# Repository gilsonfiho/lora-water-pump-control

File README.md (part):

# Controle de Bomba D'água à Distância — ESP32-C3 + LoRa

Sistema de controle remoto de bomba d'água com dois nós sem fio de longo
alcance (até ~5 km), baseado em **ESP32-C3** e módulos **LoRa EBYTE E220**
(900 MHz). O nó do reservatório mede o nível da caixa d'água e comanda, via
LoRa, o nó da bomba na captação — com confirmação (ACK), retransmissão e
**failsafe de segurança** (a bomba desliga se o enlace cair).

> **Status do projeto:** 🟡 `v0.0.1` (estruturação, pré-alpha) — esqueleto
> funcional. Arquitetura, protocolo e drivers principais implementados. Pinagem
> e modelo exato dos módulos ainda precisam ser confirmados no hardware —
> procure por `TODO(hw)` no código. Histórico em [`CHANGELOG.md`](CHANGELOG.md).
>
> A branch `feature/prototipo-bancada` roda em **modo bancada**: ver
> [Protótipo de bancada](#protótipo-de-bancada).

---

## Sumário

- [Visão geral](#visão-geral)
- [Hardware necessário](#hardware-necessário)
- [Estrutura do repositório](#estrutura-do-repositório)
- [Como compilar e gravar](#como-compilar-e-gravar)
- [Testes automatizados](#testes-automatizados)
- [Protótipo de bancada](#protótipo-de-bancada)
- [Configuração](#configuração)
- [Protocolo de comunicação](#protocolo-de-comunicação)
- [Documentação adicional](#documentação-adicional)
- [Pendências (TODOs de hardware)](#pendências-todos-de-hardware)

---

## Visão geral

| Nó | Papel | Componentes | Seleção |
|----|-------|-------------|---------|
| **Reservatório** | Transmissor | ESP32-C3, boia de nível, E220 | strap aberto |
| **Bomba** | Receptor / atuador | ESP32-C3, relé/contator, E220 | strap no GND |

**Lógica de controle (com histerese das boias):**

- Caixa **baixa** → comando **LIGAR** bomba (encher).
- Caixa **cheia** → comando **DESLIGAR** bomba.
- Nível intermediário → mantém o comando anterior (evita liga-desliga rápido).
- Falha de sensor **ou perda de enlace** → bomba **DESLIGADA** (seguro).

## Hardware necessário

- 2× **ESP32-C3** (RISC-V, Wi-Fi + BLE, baixo consumo).
- 2× módulo LoRa **EBYTE E220-900T30D** (30 dBm / 1 W) **ou** **E220-900T22D**
  (22 dBm / 160 mW) — o firmware suporta ambos (só muda a tabela de potência).
  O protótipo usa o **par T30D**, e o T22D entra como comparação no teste de
  campo.
  > ⚠️ Os E220 são **UART/TTL**, não SPI. A camada HAL abstrai isso; um driver
  > SPI SX1276/RFM95 existe como **segunda estratégia** (esqueleto).
- Sensor de nível: **boia** (padrão) — 1 ou 2 boias para histerese.
  Ultrassônico é **opcional** (flag `USE_ULTRASONIC_SENSOR`).
- 1× **relé/contator** dimensionado para a bomba (no nó da bomba).
- Alimentação **dual com failover** por nó:
  - Fonte externa (adaptador 5 V / 12 V) **+**
  - Bateria de lítio 18650 com carregador/proteção (**TP4056** ou similar);
  - Chaveamento automático fonte↔bateria (ideal-diode/diodos);
  - Monitor de tensão/corrente (ADC via divisor, ou **INA219/INA226** por I2C).
- Antenas SMA adequadas à faixa 900 MHz (ganho ~2–3 dBi).

### Ligações dos nós

| Reservatório (transmissor) | Bomba (receptor/atuador) |
|:--------------------------:|:------------------------:|
|  |  |

> Esquemático completo, pinagem detalhada e notas de projeto:
> [`assets/schematic.md`](assets/schematic.md).

### Placas (PCB)

Duas placas em KiCad 10 (`hardware/`), ESP32-C3-MINI-1 + soquete para o E220,
2 camadas. Versão atual: `hw-v0.2` (inclui o LED de RSSI).

| Emissor (reservatório) | Receptor (bomba) |
|:----------------------:|:----------------:|
|  |  |
|  |  |
|  |  |
| [STEP](hardware/fab/emissor/emissor.step) | [STEP](hardware/fab/receptor/receptor.step) |

> Decisões de projeto, regras de layout e como abrir os projetos:
> [`hardware/README.md`](hardware/README.md) e
> [`hardware/docs/decisoes.md`](hardware/docs/decisoes.md).

## Estrutura do repositório

```
lora-water-pump-control/
├── CMakeLists.txt              # projeto ESP-IDF
├── sdkconfig.defaults          # alvo esp32c3 + opções do projeto
├── README.md
├── CHANGELOG.md                # histórico de versões (SemVer)
├── docs/
│   ├── ARCHITECTURE.md         # decisões, camadas, protocolo, máquinas de estado
│   ├── context/                # notas de contexto (decisões, hardware, status)
│   └── datasheets/             # manuais dos módulos E220
├── assets/
│   ├── block-diagram.md/.svg   # diagrama de blocos da solução
│   ├── schematic.md            # esquemático elétrico (imagens + Mermaid + texto)
│   ├── schematic-power.svg     # subsistema de energia (failover + TP4056)
│   ├── schematic-reservoir.svg # ligações do nó do reservatório
│   └── schematic-pump.svg      # ligações do nó da bomba
├── components/                 # código compartilhado, em camadas
│   ├── config/                 # pinos, endereços, timeouts, perfil de RF
│   ├── platform/               # relógio monotônico (isola o ESP-IDF)
│   ├── hw/                     # abstração de hardware (interfaces + drivers)
│   ├── protocol/               # pacote, CRC, camada de enlace (ACK/retry)
│   ├── core/                   # máquinas de estado + Observer
│   └── power/                  # deep sleep + failover de energia
└── main/
    ├── main.cpp                # lê o strap e assume o papel do nó
    ├── reservoir_app.cpp       # laço do nó do reservatório
    └── pump_app.cpp            # laço do nó da bomba
```

As dependências entre camadas são declaradas em `REQUIRES`, no `CMakeLists.txt`
de cada componente — o build **impede** que `core/` ou `protocol/` alcancem um
driver concreto.

## Como compilar e gravar

O projeto é compilado e gravado pela **extensão ESP-IDF do VS Code**, com o
[ESP-IDF](https://docs.espressif.com/projects/esp-idf/) **v6.1**.

**Um único binário serve aos dois nós.** O papel é lido no boot pelo pino
`cfg::RolePins::kRoleStrap`:

| Strap | Papel |
|-------|-------|
| aberto | reservatório (transmissor) |
| ligado ao GND | bomba (receptor/atuador) |

O aberto virar reservatório é proposital: é o papel que não aciona o relé, então
um strap solto nunca faz um nó assumir o comando da bomba.

### Preparação (uma vez por máquina)

1. Instale a extensão **ESP-IDF** (`espressif.esp-idf-extension`) no VS Code.
2. `Ctrl+Shift+P` → **ESP-IDF: Configure ESP-IDF Extension**. O instalador
   (EIM) baixa o ESP-IDF **v6.1** e as ferramentas (no Windows, em `C:\esp\v6.1`
   e `C:\Espressif`).
3. Abra a pasta do repositório no VS Code.
4. `Ctrl+Shift+P` → **ESP-IDF: Select Current ESP-IDF Version** → **v6.1**.

### Configuração do projeto (uma vez)

Pela barra de status, na parte de baixo da janela, ou pela paleta
(`Ctrl+Shift+P`):

| Ajuste | Comando | Valor |
|--------|---------|-------|
| Alvo | **ESP-IDF: Set Espressif Device Target** | `esp32c3` → *ESP32-C3 chip (via builtin USB-JTAG)* |
| Método de gravação | **ESP-IDF: Select Flash Method** | `UART` |
| Porta | **ESP-IDF: Select Port to Use** | a COM da placa (ex.: `COM3`) |

Trocar o alvo recria o `sdkconfig` a partir do `sdkconfig.defaults`. A porta
aparece no Gerenciador de Dispositivos (o USB Serial/JTAG do C3 costuma se
chamar "Dispositivo serial USB").

### Comandos da extensão

| Ação | Atalho | Comando da paleta |
|------|--------|-------------------|
| Compilar | `Ctrl+E B` | ESP-IDF: Build your Project |
| Gravar | `Ctrl+E F` | ESP-IDF: Flash your Project |
| Monitor serial | `Ctrl+E M` | ESP-IDF: Monitor Device |
| **Tudo de uma vez** | `Ctrl+E D` | ESP-IDF: Build, Flash and Start a Monitor on your Device |
| Terminal com o ambiente do IDF | — | ESP-IDF: Open ESP-IDF Terminal |
| Opções do `sdkconfig` | `Ctrl+E G` | ESP-IDF: SDK Configuration Editor |
| Limpar o build | — | ESP-IDF: Full Clean Project |

Os mesmos botões aparecem na barra de status (chave inglesa = compilar, raio =
gravar, tela = monitor). Para sair do monitor, use `Ctrl+]`.

Depois de criar, renomear ou apagar um componente, ou de mexer em `REQUIRES`,
rode **Full Clean Project** antes de compilar. O CMake só descobre os
componentes na configuração.

### Passo a passo: gravar o reservatório e a bomba

As duas placas recebem **o mesmo binário**. O que decide o papel é só o fio no
**GPIO 3**, lido **uma vez, no boot**:

| | Reservatório (transmissor) | Bomba (receptor) |
|---|---|---|
| GPIO 3 | **aberto** (nada ligado) | **ligado ao GND** |
| Periférico | chave de nível no GPIO 1 | LED + 330 Ω no GPIO 1 |
| LED de RSSI (opcional) | LED + 330 Ω no GPIO 0 | LED + 330 Ω no GPIO 0 |
| Tag no log | `reservatorio` | `bomba` |

#### 0. Antes de ligar qualquer placa

- **Antena rosqueada em cada E220.** O firmware transmite logo depois de
  gravar, e sem antena o PA do módulo pode queimar.
- **Strap já no lugar.** Na placa da bomba, jumper do GPIO 3 ao GND **antes**
  de ligar o USB. O pino só é lido no boot: mudar o strap com a placa ligada não
  tem efeito até o próximo reset.
- **Nós a ≥ 3 m um do outro** (T30D, ver
  [Protótipo de bancada](#protótipo-de-bancada)). Isso vale também durante a
  gravação, porque cada placa começa a transmitir assim que o firmware sobe.
- **Etiquete as placas** ("R" e "B"). Com o mesmo binário, só o strap e a
  etiqueta diferenciam uma da outra.

#### 1. Descobrir a porta de cada placa

Conecte **só a placa do reservatório** e veja qual COM aparece em
**ESP-IDF: Select Port to Use** (ou no Gerenciador de Dispositivos, em
"Portas (COM e LPT)"). Anote. Depois conecte a da bomba e anote a COM nova.
Exemplo usado abaixo: reservatório = `COM3`, bomba = `COM4`.

> A porta não aparece? Quase sempre é cabo USB só de carga. Troque por um
> cabo de dados.

#### 2. Compilar (uma vez para as duas)

`Ctrl+E B`. O terminal deve terminar com `Project build complete`. O binário
vai para `build/` e serve às duas placas.

#### 3. Gravar e conferir o reservatório (transmissor)

1. **Select Port to Use** → `COM3` (reservatório).
2. `Ctrl+E F` para gravar. No fim, a placa reinicia sozinha.
3. `Ctrl+E M` para abrir o monitor. O boot deve mostrar:

   ```text
   I (…) main: strap aberto -> papel RESERVATORIO
   I (…) reservatorio: iniciando...
   I (…) reservatorio: pronto (bancada: chave no GPIO 1, ciclo de 2000 ms)
   ```

4. Mexa na chave. Deve aparecer uma linha como
   `reservatorio: chave: CHEIA (para) -> BAIXA (pedindo agua)`.
5. `Ctrl+]` para fechar o monitor antes de ir para a outra placa.

#### 4. Gravar e conferir a bomba (receptor)

1. **Select Port to Use** → `COM4` (bomba).
2. `Ctrl+E F` para gravar.
3. `Ctrl+E M` para abrir o monitor. O boot deve mostrar:

   ```text
   I (…) main: strap em GND -> papel BOMBA
   I (…) bomba: iniciando...
   I (…) bomba: pronto (bancada: LED no GPIO 1, failsafe em 15000 ms)
   I (…) bomba: estado -> OCIOSO (saida=DESLIGADA)
   ```

   Se o reservatório estiver desligado, em ~15 s aparece
   `estado -> ENLACE PERDIDO (failsafe)`. **É o esperado:** sem tráfego, a
   bomba desliga.

Se aparecer `papel RESERVATORIO` na placa da bomba, o GPIO 3 não está no GND.
Corrija o jumper e aperte **RST**.

#### 5. Ver os dois logs ao mesmo tempo

O monitor da extensão acompanha uma porta por vez. Para o segundo nó:

1. **ESP-IDF: Open ESP-IDF Terminal** (abre um terminal com o ambiente
   ativado).
2. Rode `idf.py -p COM3 monitor` (reservatório).
3. Deixe o monitor da extensão na `COM4` (bomba).

Cada monitor reinicia a placa ao abrir. Isso é normal.

#### 6. Conferir que os dois conversam

Com os dois monitores abertos, feche a chave do reservatório. Em ~2 s a bomba
loga `estado -> BOMBEANDO (saida=LIGADA)` e o LED acende. A partir daí, siga o
[roteiro de validação](#roteiro-de-validação).

#### Problemas comuns

| Sintoma | Causa provável | O que fazer |
|---|---|---|
| Gravação falha com `Failed to connect` | Placa não entrou em modo de gravação | Segure **BOOT**, aperte e solte **RST**, solte **BOOT** e grave de novo |
| Os dois nós logam `RESERVATORIO` | GPIO 3 da bomba solto | Jumper ao GND e **RST** |
| `FALHA ao iniciar o radio E220` | Módulo sem alimentação, TX/RX invertidos ou `AUX` solto | VCC em 5 V, TXD do E220 → GPIO 4, RXD → GPIO 5, AUX → GPIO 10 |
| Placa reinicia ou a COM some a cada transmissão | Pico de corrente do T30D derruba a USB | Confira o 1000 µF junto ao VCC; se persistir, fonte de 5 V externa |
| Bomba sempre em `ENLACE PERDIDO` com o reservatório ligado | Nós com firmwares ou canais diferentes, ou antena solta | Regrave **as duas** placas com o mesmo build |
| Porta COM não aparece | Cabo só de carga | Cabo USB de dados |

> Pelo terminal (CI, scripts): ative o ambiente com
> `. C:\Espressif\tools\Microsoft.v6.1.PowerShell_profile.ps1` e use
> `idf.py build` / `idf.py -p COMx flash monitor`.

> ⚠️ Os dois nós gravam a configuração do E220 (canal, taxa aérea) a cada boot.
> Ao mudar algo em `RadioConfig.h`, **regrave as duas placas**: em
> configurações diferentes elas não se comunicam, e o sintoma é o mesmo de um
> enlace caído.

## Testes automatizados

A suíte roda **no QEMU, sem placa nenhuma**, em poucos segundos. São 60 casos
(Unity) sobre `protocol/` e `core/`, com rádio, atuador, sensor e bateria
falsos, e um **relógio controlado pelo teste** — por isso um failsafe de 45 s ou
um bloqueio de 30 min são verificados sem esperar nada.

```powershell
# Uma vez por máquina:
python $env:IDF_PATH\tools\idf_tools.py install qemu-riscv32

# A cada rodada, da raiz do repositório:
.\test\run-tests.ps1            # saída completa (inclui o boot do IDF)
.\test\run-tests.ps1 -Quiet     # só os casos e o resumo
```

Uma rodada leva cerca de 12 s. A saída sai **ao vivo**, caso por caso:

```text
== compilando os testes...
== rodando no QEMU...
./main/test_packet.cpp:29:CRC-16/CCITT-FALSE confere com o vetor conhecido:PASS
...
60 Tests 0 Failures 0 Ignored
==== FIM DOS TESTES: 0 falha(s) ====
== todos os testes passaram
```

Falha aparece em vermelho, com arquivo, linha, nome do caso e o que era
esperado:

```text
./main/test_pump_controller.cpp:186:nao bloqueia pouco antes do limite:FAIL: Expected 2 Was 3
```

**O script devolve código de saída** (0 se tudo passou, 1 se houve falha ou
travamento), então serve para CI ou para um hook de pre-commit. Ele também
cuida de três armadilhas do ambiente: acrescenta o QEMU ao PATH (o perfil do
EIM é gerado antes de o QEMU existir), encerra o emulador junto com o processo
pai (senão sobra um `qemu-system-riscv32` órfão segurando a porta 5555, e a
rodada seguinte não sobe) e, em caso de falha, imprime as últimas linhas do log
e onde ele está.

Para rodar na placa em vez do QEMU: `idf.py -C test -p COMx flash monitor`.

| Arquivo | Cobre |
|---------|-------|
| [`test/main/test_packet.cpp`](test/main/test_packet.cpp) | CRC-16 (vetor conhecido), ida e volta do quadro, CRC corrompido, truncamento, SYNC/versão inválidos, payload máximo |
| [`test/main/test_messages.cpp`](test/main/test_messages.cpp) | Builders e parsers de cada tipo, incluindo `BOMBA_STATUS` |
| [`test/main/test_link_layer.cpp`](test/main/test_link_layer.cpp) | ACK, retransmissão com o mesmo SEQ, timeout, auto-ACK, filtro de endereço, broadcast, ressincronização por SYNC, par de nós em loopback, e a regressão do relógio de retransmissão |
| [`test/main/test_pump_controller.cpp`](test/main/test_pump_controller.cpp) | Os dois failsafes, e o latch da issue #9 (inclusive sobrevivendo à queda do enlace) |
| [`test/main/test_reservoir_controller.cpp`](test/main/test_reservoir_controller.cpp) | Decisão de nível com histerese, sensor falho, heartbeat, telemetria |

Os testes **não substituem a bancada**: nada aqui exercita o E220, os GPIOs, a
alimentação ou o alcance. Eles cobrem a lógica; o hardware é a bancada.

## Protótipo de bancada

Primeira etapa de validação: **enlace, protocolo e failsafe na mesa, sem água,
sem bomba e sem carga AC**. É o critério para a versão `0.1.0` (primeiro alpha).
Roteiro completo em [`docs/context/bancada.md`](docs/context/bancada.md).

### O que muda em relação ao campo

| Campo | Bancada | Implementação |
|-------|---------|---------------|
| Boias | **Chave que trava** (gangorra/alavanca) | `BenchSwitchLevelSensor` |
| Contator + bomba | **LED + resistor de 330 Ω** | `RelayPumpActuator` (mesmo driver) |
| Bateria + divisor | **Stub fixo** (fonte externa, 100%) | `StubBatteryMonitor` |
| Tempos de campo | **Tempos curtos** | `BENCH_PROFILE` em `NodeConfig.h` |
| TX a 30 dBm | **TX a 21 dBm** (mínimo do T30D) | `cfg::kTxPower` em `RadioConfig.h` |

Controladores, protocolo e `LinkLayer` **não mudam**: só trocam as
implementações de `ILevelSensor` e `IBatteryMonitor`. O `BENCH_PROFILE` vem
ligado. Para os tempos e a potência de campo, troque `#define BENCH_PROFILE 1`
por `0` em `NodeConfig.h`. (`idf.py build -DBENCH_PROFILE=0` **não** funciona:
cria uma variável do CMake, não um `#define` do compilador.)

| | Bancada | Campo |
|---|---|---|
| Ciclo do reservatório | 2 s | 10 s |
| Heartbeat | 5 s | 15 s |
| Failsafe (perda de enlace) | 15 s | 45 s |
| Telemetria de bateria | 15 s | 60 s |
| Potência de TX (T30D) | 21 dBm | 30 dBm |

### Material

- 2× devkit ESP32-C3 e 2× **E220-900T30D**, cada módulo com a **sua antena**
  de 900 MHz (conector SMA).
- 2× protoboard, jumpers e 2 cabos USB de dados.
- 2× eletrolítico de **1000 µF** (≥ 10 V) + 2× cerâmico de 100 nF, um par junto
  ao VCC de cada E220. **Obrigatório**: o T30D puxa picos de corrente que a USB
  sozinha não segura.
- 1× chave que trava (não serve botão momentâneo: a leitura é uma vez por
  ciclo).
- 1× LED + resistor de 330 Ω.

O par T22D fica para o teste de campo, como comparação.

### Ligações

As duas placas recebem **o mesmo binário**; só o strap muda.

| Função | GPIO do ESP32-C3 | Ligação |
|--------|------------------|---------|
| E220 `TXD` | 4 (RX do ESP) | |
| E220 `RXD` | 5 (TX do ESP) | |
| E220 `M0` / `M1` | 6 / 7 | |
| E220 `AUX` | 10 | |
| E220 `VCC` | pino **5V** (VBUS) | 1000 µF + 100 nF junto ao módulo |
| E220 `GND` | GND | |
| Strap de papel | 3 | aberto = reservatório · GND = bomba |
| Chave de nível (só reservatório) | 1 | outro lado no GND |
| LED da bomba (só bomba) | 1 | LED + 330 Ω para o GND |
| LED de RSSI (os dois nós) | 0 | LED + 330 Ω para o GND |

### Antes de energizar

- **Nunca ligue um E220 sem antena.** O firmware transmite logo no boot, e sem
  carga a potência refletida pode danificar o PA.
- **Nós a ≥ 3 m um do outro, obrigatoriamente.** O T30D não desce abaixo de
  21 dBm, e o receptor **pode queimar** com mais de +10 dBm na entrada. A 10 cm
  chegam ~+13 dBm; a 3 m, ~−15 dBm. Pontas opostas da sala ou salas
  diferentes.
- **VCC em 5 V, sinais em 3,3 V.** O T30D precisa de 5 V para a potência
  nominal, mas UART, M0, M1 e AUX vão direto ao ESP32-C3. O manual avisa que
  TTL de 5 V pode queimar o módulo.
- **A alimentação pela USB é um improviso.** Se o ESP resetar ou a porta USB
  cair a cada transmissão, alimente o E220 com uma fonte de 5 V externa
  (≥ 1 A), com GND comum ao devkit.
- **Canal 55 (905,125 MHz)**, dentro da faixa permitida pela ANATEL. O canal de
  fábrica do E220 (873,125 MHz) não é permitido no Brasil. Detalhes em
  [`docs/context/hardware.md`](docs/context/hardware.md).

### Roteiro de validação

1. **Boot:** cada nó loga o papel que assumiu.
2. **Rádio:** nenhum nó pode logar `FALHA ao iniciar o radio E220`.
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
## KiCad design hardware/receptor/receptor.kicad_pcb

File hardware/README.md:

# Hardware (PCB)

Duas placas, `emissor/` e `receptor/` (um projeto KiCad cada). Projeto KiCad **10** (10.0.x; formatos de arquivo da série 10, que as versões anteriores não abrem) da placa dos dois nós. Uma única PCB, com
componentes marcados DNP conforme o papel (reservatório ou bomba).

> **Status:** estrutura criada. Nenhum esquemático ainda: o escopo depende das
> decisões em aberto de [`docs/decisoes.md`](docs/decisoes.md).

## Estrutura

| Pasta | Conteúdo |
|-------|----------|
| `./` | projeto KiCad (`.kicad_pro`, `.kicad_sch`, `.kicad_pcb`) |
| `libs/` | símbolos, footprints e modelos 3D do projeto (versionados) |
| `fab/` | saídas de fabricação: Gerber, furação, BOM por variante, CPL, PDF, STEP, renders |
| `docs/` | decisões de projeto e notas |

## Convenções

- Versões de hardware com tag `hw-vX.Y`, para não colidir com o SemVer do
  firmware (`vX.Y.Z`). Registradas no [`CHANGELOG.md`](../CHANGELOG.md).
- Decisões e motivos em [`docs/decisoes.md`](docs/decisoes.md).
- Pinagem do ESP32-C3 final só vai ao `PinConfig.h` depois de aprovada, em
  commit separado.
- **O E220 transmite logo no boot e nunca pode ficar sem antena.**

## O que não vai ao Git

- `libs/vendor/` e `docs/datasheets/`: arquivos baixados de terceiros (STEP,
  footprints, datasheets). A origem de cada um fica no `SOURCES.md` da pasta.
  Os datasheets do E220, já no repositório, ficam em `../docs/datasheets/`.
- Versionados: o projeto KiCad e as bibliotecas **próprias** (`libs/symbols`,
  `libs/footprints`), que usam caminhos relativos (`${KIPRJMOD}`).

## Como abrir

- Emissor: `emissor/emissor.kicad_pro`. Receptor: `receptor/receptor.kicad_pro`.
- No editor de PCB, **View > 3D Viewer** (Alt+3) mostra a placa em 3D.
- Imagens e STEP prontos em `fab/emissor/` e `fab/receptor/`.

## Edicao

Os arquivos KiCad (`*.kicad_sch`, `*.kicad_pcb`, `libs/`) sao a fonte: edite direto no KiCad.
Os scripts que geraram o projeto inicial (`hardware/tools/`) **nao sao versionados**
(estao no `.gitignore`); quem os tiver localmente nao deve rodar o `build_pcb.py`
sobre uma placa editada a mao, porque ele sobrescreve o roteamento.

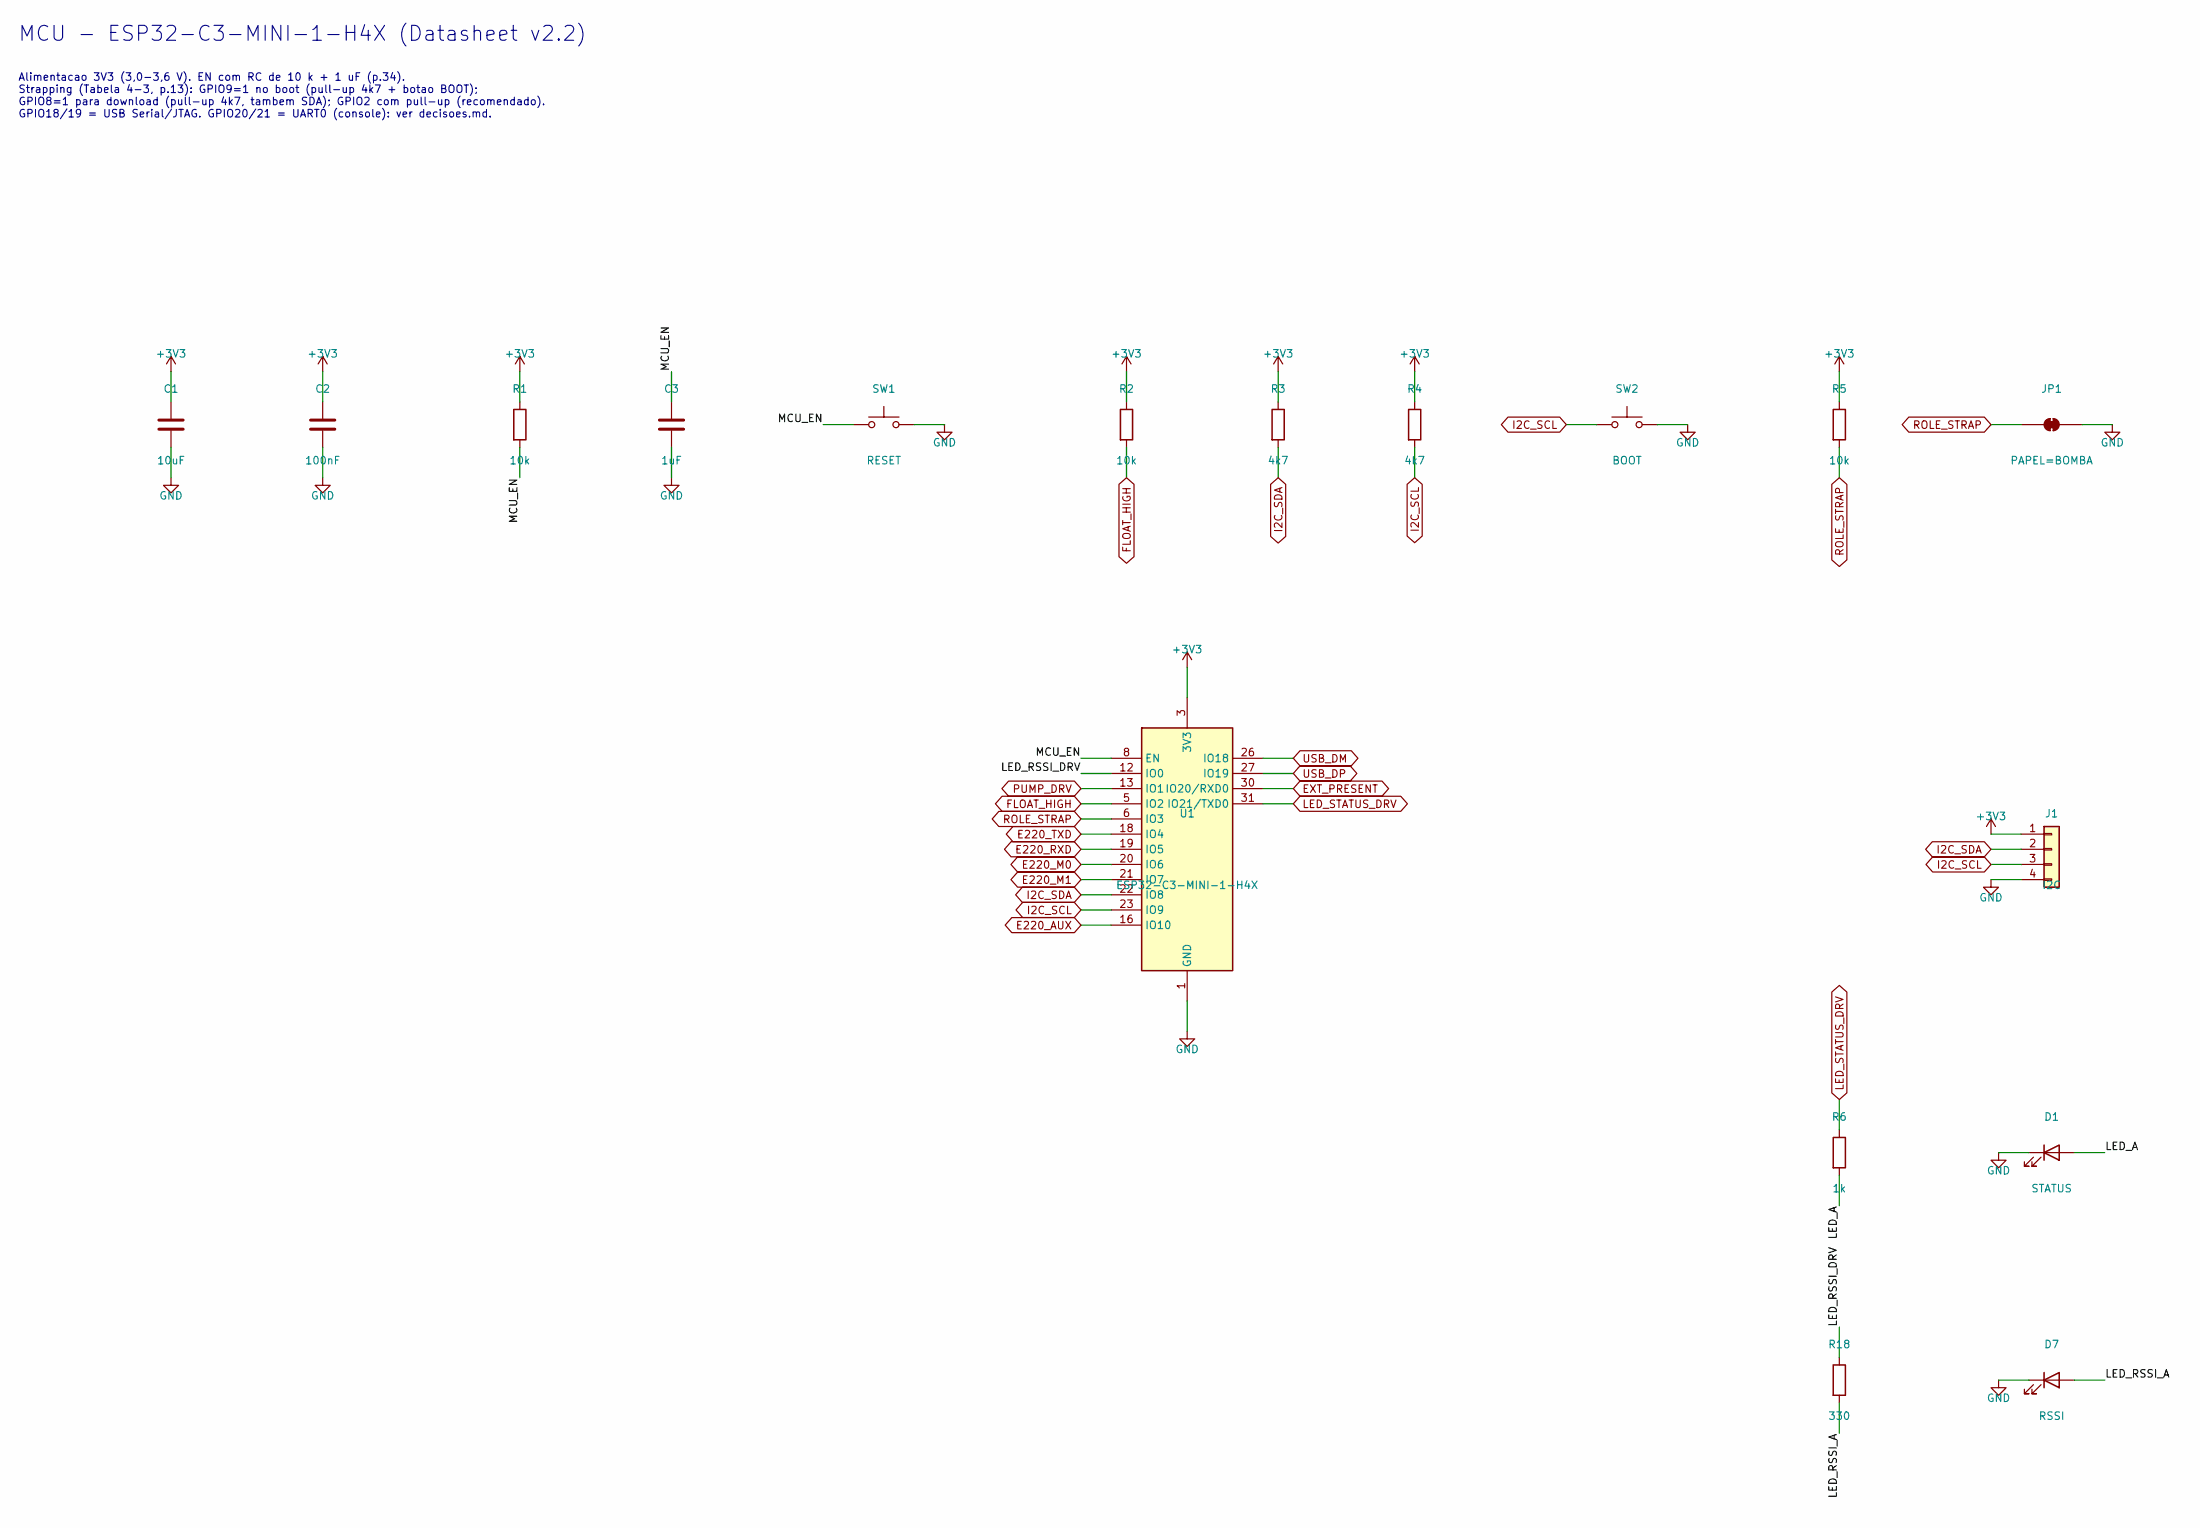
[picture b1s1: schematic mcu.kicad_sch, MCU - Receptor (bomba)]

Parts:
C1: 10uF; C_0603_1608Metric; MPN CL10A106KP8NNNC
C2: 100nF; C_0603_1608Metric; MPN CL10B104KB8NNNC
C3: 1uF; C_0603_1608Metric; MPN CL10A105KB8NNNC
D1: STATUS; LED_0603_1608Metric; MPN APT1608SGC
D7: RSSI; LED_0603_1608Metric; MPN TODO(hw): LED 0603 ambar
J1: I2C; PinHeader_1x04_P2.54mm_Vertical; MPN PinHeader_1x04_P2.54mm
JP1: PAPEL=BOMBA; SolderJumper-2_P1.3mm_Bridged_RoundedPad1.0x1.5mm
R1, R2, R5: 10k; R_0603_1608Metric; MPN RC0603FR-0710KL
R3, R4: 4k7; R_0603_1608Metric; MPN RC0603FR-074K7L
R6: 1k; R_0603_1608Metric; MPN RC0603FR-071KL
R18: 330; R_0603_1608Metric; MPN RC0603FR-07330RL
SW1: RESET; SW_SPST_TL3342; MPN TL3342F160QG
SW2: BOOT; SW_SPST_TL3342; MPN TL3342F160QG
U1: ESP32-C3-MINI-1-H4X; ESP32-C3-MINI-1; MPN ESP32-C3-MINI-1-H4X

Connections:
+3V3: C1.1, C2.1, J1.1, R1.1, R2.1, R3.1, R4.1, R5.1, U1.3 (3V3); also elsewhere on the board
/MCU/LED_A: D1.2 (A), R6.2
/MCU/LED_RSSI_A: D7.2 (A), R18.2
/MCU/LED_RSSI_DRV: R18.1, U1.12 (IO0)
/MCU/MCU_EN: C3.1, R1.2, SW1.1, U1.8 (EN)
E220_AUX: U1.16 (IO10); also elsewhere on the board
E220_M0: U1.20 (IO6); also elsewhere on the board
E220_M1: U1.21 (IO7); also elsewhere on the board
E220_RXD: U1.19 (IO5); also elsewhere on the board
E220_TXD: U1.18 (IO4); also elsewhere on the board
EXT_PRESENT: U1.30 (IO20/RXD0); also elsewhere on the board
FLOAT_HIGH: R2.2, U1.5 (IO2)
GND: C1.2, C2.2, C3.2, D1.1 (K), D7.1 (K), J1.4, JP1.2 (B), SW1.2, SW2.2, U1.1 (GND), U1.2 (GND), U1.11 (GND), U1.14 (GND), U1.36 (GND), U1.37 (GND), U1.38 (GND), U1.39 (GND), U1.40 (GND), U1.41 (GND), U1.42 (GND), U1.43 (GND), U1.44 (GND), U1.45 (GND), U1.46 (GND), U1.47 (GND), U1.48 (GND), U1.49 (GND), U1.50 (GND), U1.51 (GND), U1.52 (GND), U1.53 (GND); also elsewhere on the board
I2C_SCL: J1.3, R4.2, SW2.1, U1.23 (IO9)
I2C_SDA: J1.2, R3.2, U1.22 (IO8)
LED_STATUS_DRV: R6.1, U1.31 (IO21/TXD0)
PUMP_DRV: U1.13 (IO1); also elsewhere on the board
ROLE_STRAP: JP1.1 (A), R5.2, U1.6 (IO3)
USB_DM: U1.26 (IO18); also elsewhere on the board
USB_DP: U1.27 (IO19); also elsewhere on the board

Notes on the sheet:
MCU - ESP32-C3-MINI-1-H4X (Datasheet v2.2)
Alimentacao 3V3 (3,0-3,6 V). EN com RC de 10 k + 1 uF (p.34). Strapping (Tabela 4-3, p.13): GPIO9=1 no boot (pull-up 4k7 + botao BOOT); GPIO8=1 para download (pull-up 4k7, tambem SDA); GPIO2 com pull-up (recomendado). GPIO18/19 = USB Serial/JTAG. GPIO20/21 = UART0 (console): ver decisoes.md.

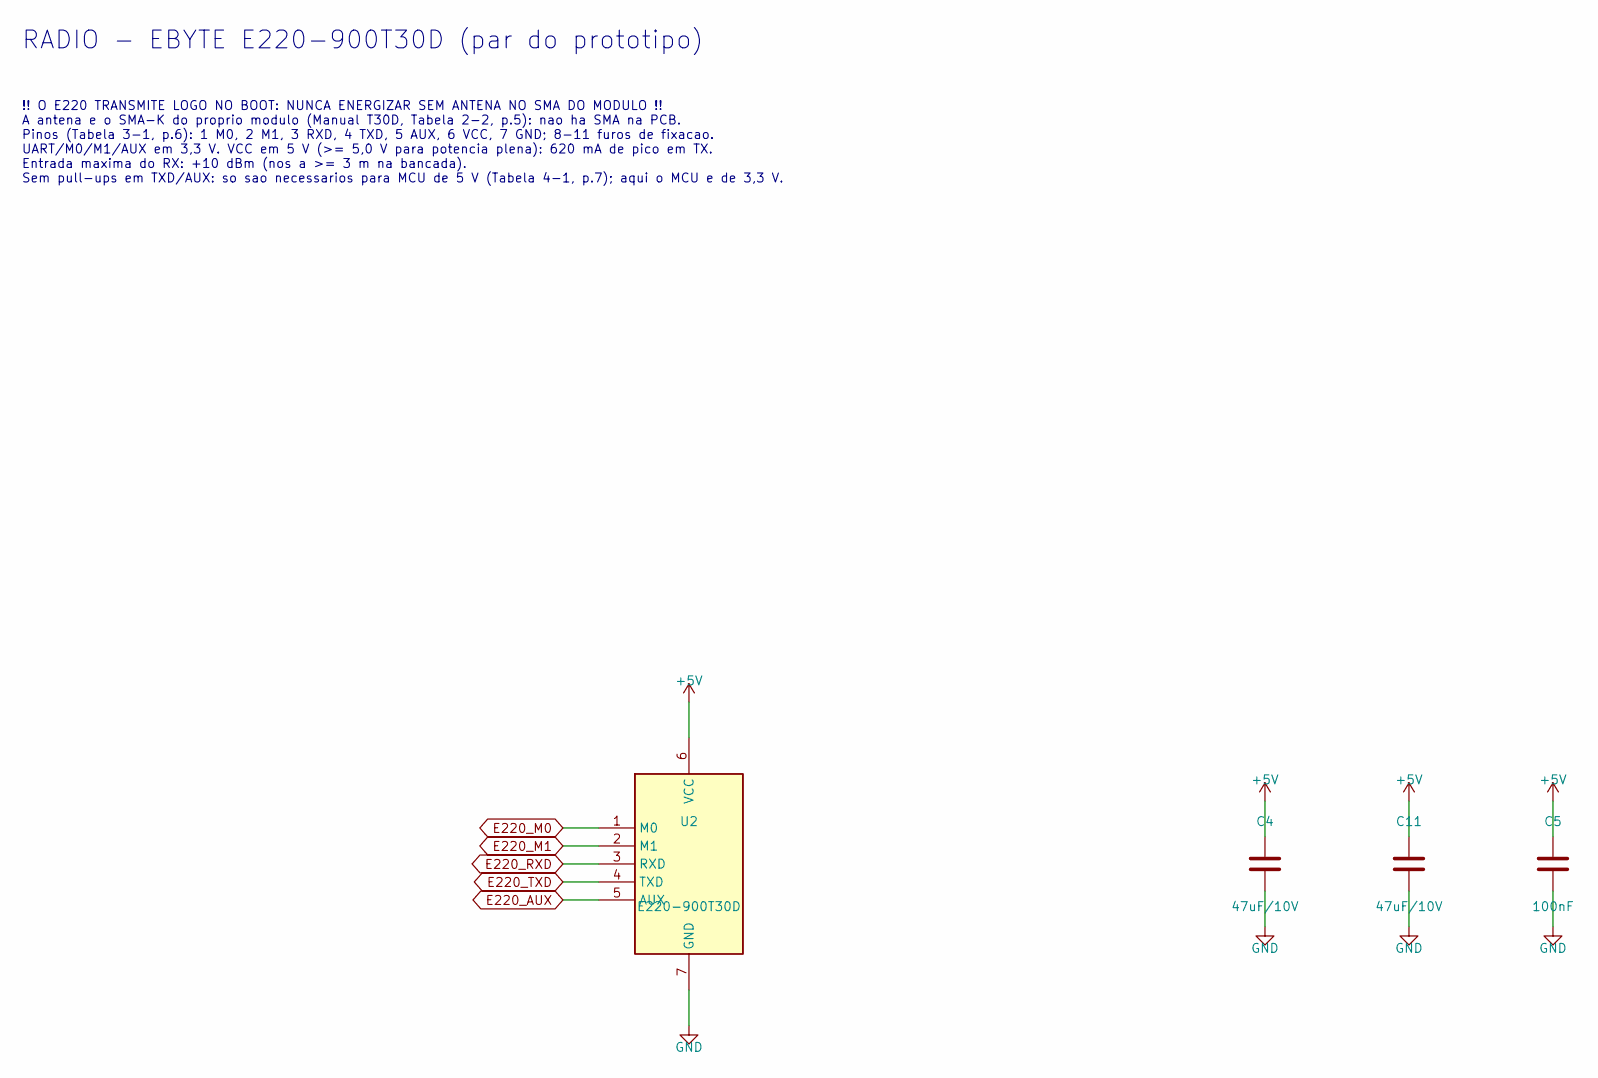
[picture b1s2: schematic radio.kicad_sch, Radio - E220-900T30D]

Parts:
C4, C11: 47uF/10V; C_1210_3225Metric; MPN CL32A476MPVNNNE
C5: 100nF; C_0603_1608Metric; MPN CL10B104KB8NNNC
U2: E220-900T30D; MPN E220-900T30D

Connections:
+5V: C4.1, C5.1, C11.1, U2.6 (VCC); also elsewhere on the board
E220_AUX: U2.5 (AUX); also elsewhere on the board
E220_M0: U2.1 (M0); also elsewhere on the board
E220_M1: U2.2 (M1); also elsewhere on the board
E220_RXD: U2.3 (RXD); also elsewhere on the board
E220_TXD: U2.4 (TXD); also elsewhere on the board
GND: C4.2, C5.2, C11.2, U2.7 (GND); also elsewhere on the board

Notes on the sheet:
RADIO - EBYTE E220-900T30D (par do prototipo)
!! O E220 TRANSMITE LOGO NO BOOT: NUNCA ENERGIZAR SEM ANTENA NO SMA DO MODULO !! A antena e o SMA-K do proprio modulo (Manual T30D, Tabela 2-2, p.5): nao ha SMA na PCB. Pinos (Tabela 3-1, p.6): 1 M0, 2 M1, 3 RXD, 4 TXD, 5 AUX, 6 VCC, 7 GND; 8-11 furos de fixacao. UART/M0/M1/AUX em 3,3 V. VCC em 5 V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

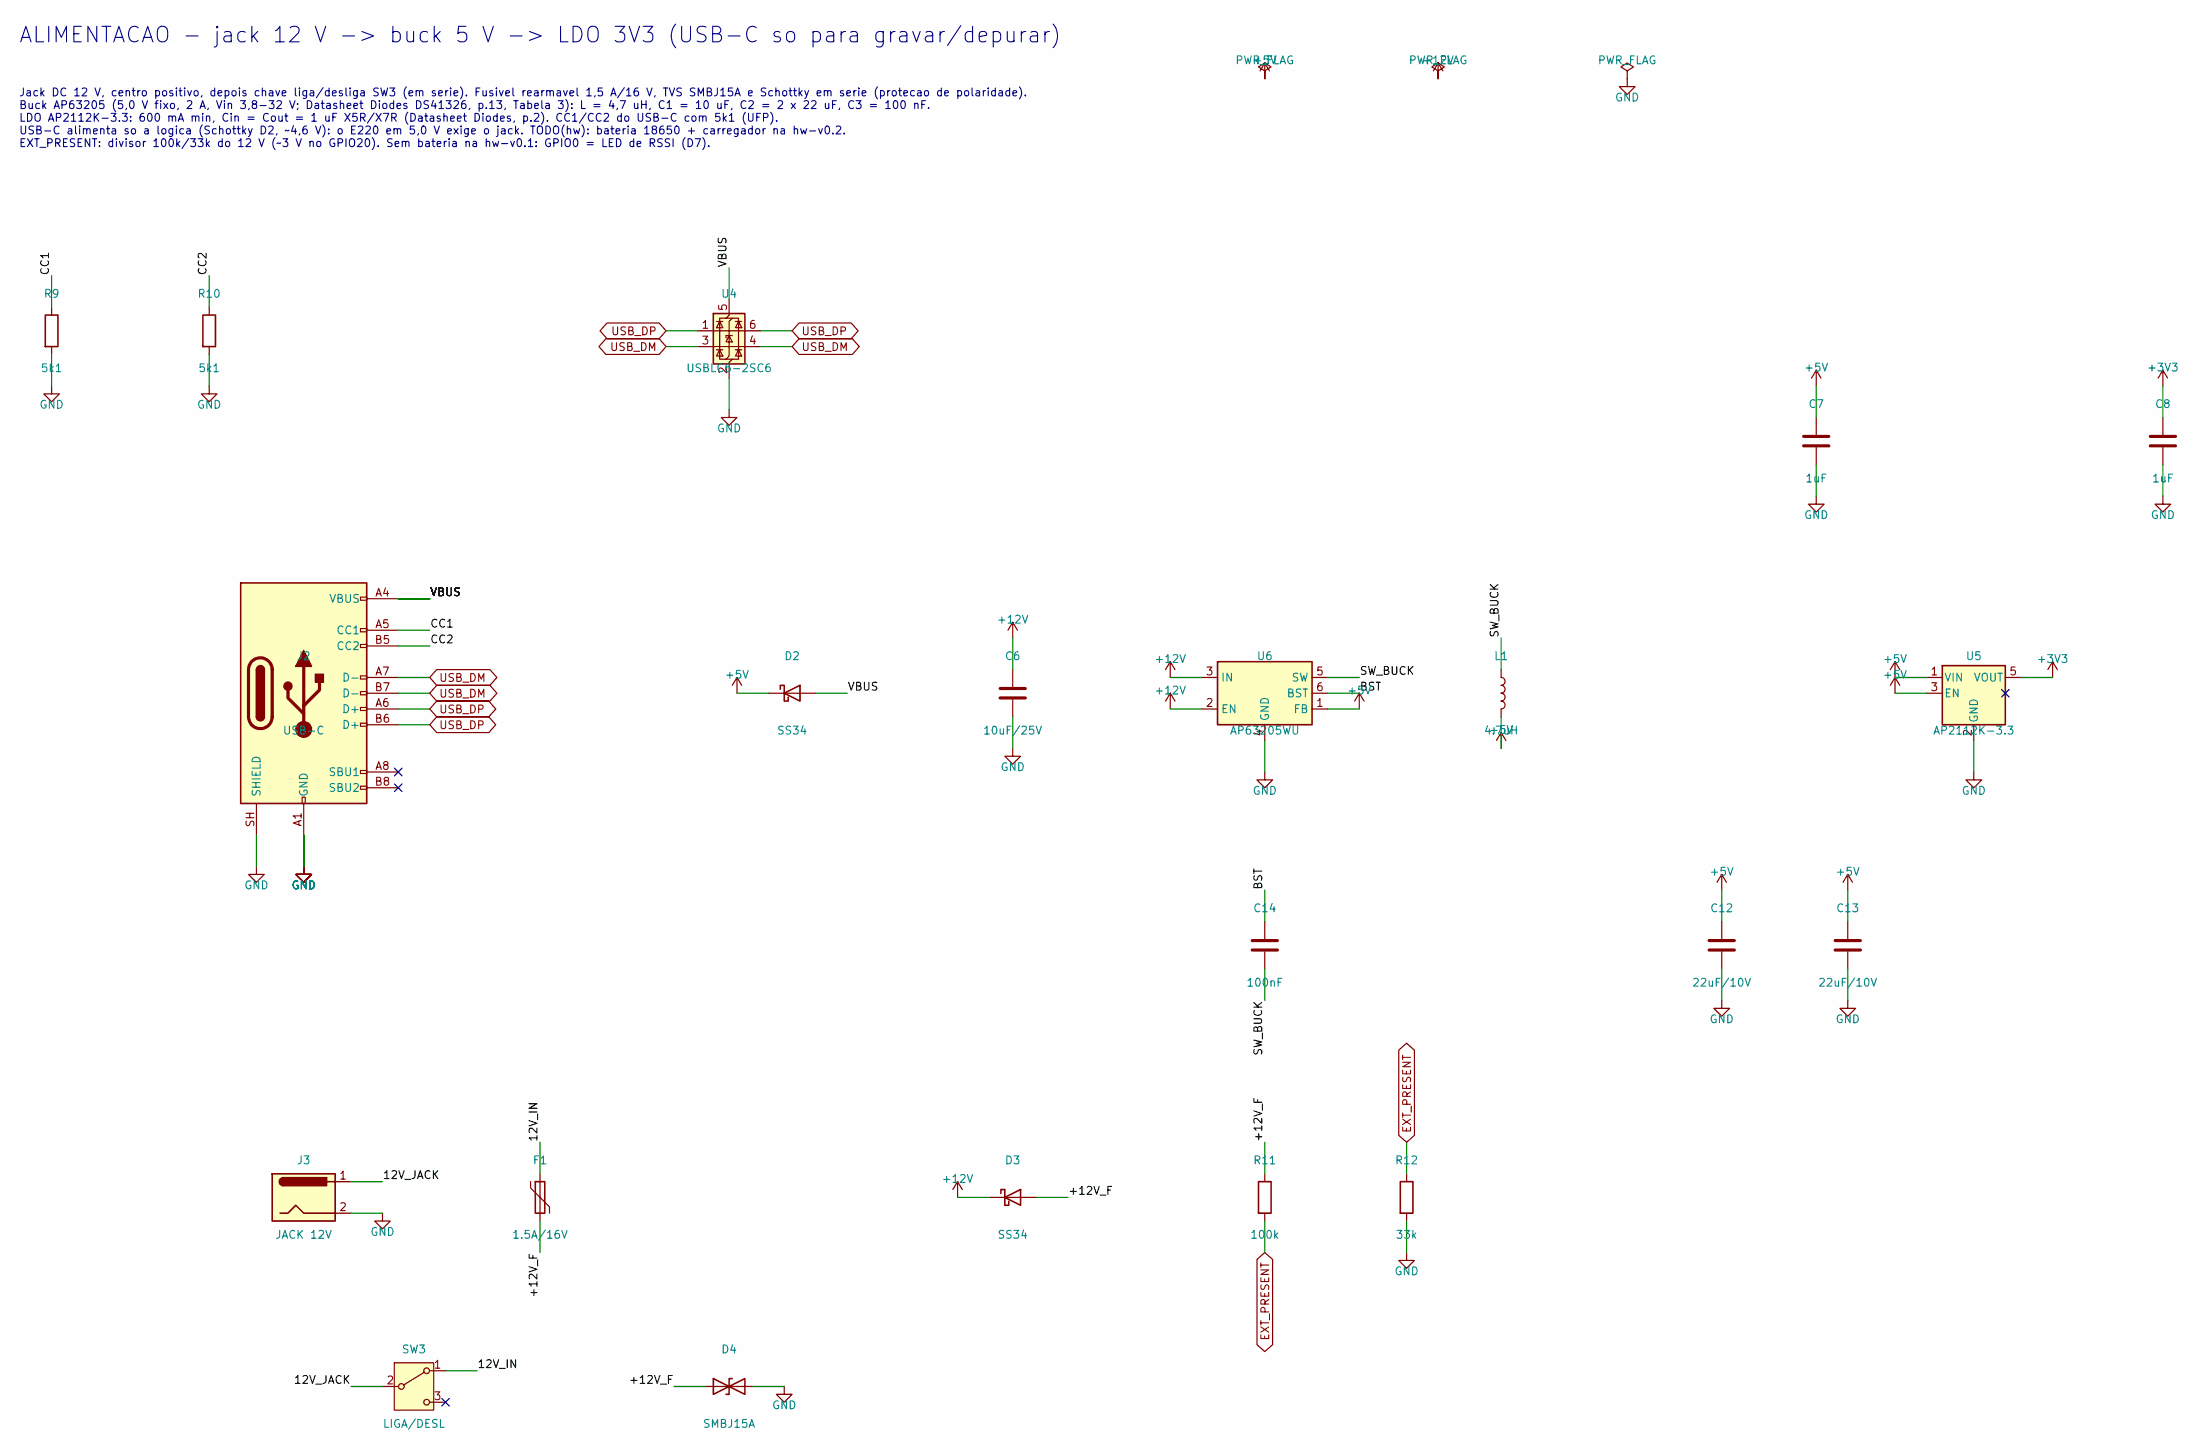
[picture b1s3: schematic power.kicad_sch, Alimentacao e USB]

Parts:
C6: 10uF/25V; C_0805_2012Metric; MPN CL21A106KAYNNNE
C7, C8: 1uF; C_0603_1608Metric; MPN CL10A105KB8NNNC
C12, C13: 22uF/10V; C_0805_2012Metric; MPN CL21A226MPQNNNE
C14: 100nF; C_0603_1608Metric; MPN CL10B104KB8NNNC
D2, D3: SS34; D_SMA; MPN SS34
D4: SMBJ15A; D_SMB; MPN SMBJ15A
F1: 1.5A/16V; Fuse_1206_3216Metric; MPN MF-MSMF150/16X-2
J2: USB-C; USB_C_Receptacle_HRO_TYPE-C-31-M-12; MPN TYPE-C-31-M-12
J3: JACK 12V; BarrelJack_CUI_PJ-102AH_Horizontal; MPN PJ-102AH
L1: 4.7uH; L_Taiyo-Yuden_NR-60xx; MPN NR6045T4R7M
R9, R10: 5k1; R_0603_1608Metric; MPN RC0603FR-075K1L
R11: 100k; R_0603_1608Metric; MPN RC0603FR-07100KL
R12: 33k; R_0603_1608Metric; MPN RC0603FR-0733KL
SW3: LIGA/DESL; SW_Slide_SPDT_Angled_CK_OS102011MA1Q; MPN TODO(hw): chave deslizante >= 2 A / 16 V
U4: USBLC6-2SC6; SOT-23-6; MPN USBLC6-2SC6
U5: AP2112K-3.3; SOT-23-5; MPN AP2112K-3.3TRG1
U6: AP63205WU; TSOT-23-6; MPN AP63205WU-7

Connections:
+3V3: C8.1, U5.5 (VOUT); also elsewhere on the board
+5V: C7.1, C12.1, C13.1, D2.1 (K), L1.2, U5.1 (VIN), U5.3 (EN), U6.1 (FB); also elsewhere on the board
+12V: C6.1, D3.1 (K), U6.2 (EN), U6.3 (IN); also elsewhere on the board
/Alimentacao/12V_IN: F1.1, SW3.1 (A)
/Alimentacao/12V_JACK: J3.1, SW3.2 (B)
/Alimentacao/+12V_F: D3.2 (A), D4.1 (A1), F1.2, R11.1
/Alimentacao/BST: C14.1, U6.6 (BST)
/Alimentacao/CC1: J2.A5 (CC1), R9.1
/Alimentacao/CC2: J2.B5 (CC2), R10.1
/Alimentacao/SW_BUCK: C14.2, L1.1, U6.5 (SW)
/Alimentacao/VBUS: D2.2 (A), J2.A4 (VBUS), J2.A9 (VBUS), J2.B4 (VBUS), J2.B9 (VBUS), U4.5 (VBUS)
EXT_PRESENT: R11.2, R12.1; also elsewhere on the board
GND: C6.2, C7.2, C8.2, C12.2, C13.2, D4.2 (A2), J2.A1 (GND), J2.A12 (GND), J2.B1 (GND), J2.B12 (GND), J2.SH (SHIELD), J3.2, R9.2, R10.2, R12.2, U4.2 (GND), U5.2 (GND), U6.4 (GND); also elsewhere on the board
USB_DM: J2.A7 (D-), J2.B7 (D-), U4.3 (I/O2), U4.4 (I/O2); also elsewhere on the board
USB_DP: J2.A6 (D+), J2.B6 (D+), U4.1 (I/O1), U4.6 (I/O1); also elsewhere on the board

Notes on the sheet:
ALIMENTACAO - jack 12 V -> buck 5 V -> LDO 3V3 (USB-C so para gravar/depurar)
Jack DC 12 V, centro positivo, depois chave liga/desliga SW3 (em serie). Fusivel rearmavel 1,5 A/16 V, TVS SMBJ15A e Schottky em serie (protecao de polaridade). Buck AP63205 (5,0 V fixo, 2 A, Vin 3,8-32 V; Datasheet Diodes DS41326, p.13, Tabela 3): L = 4,7 uH, C1 = 10 uF, C2 = 2 x 22 uF, C3 = 100 n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

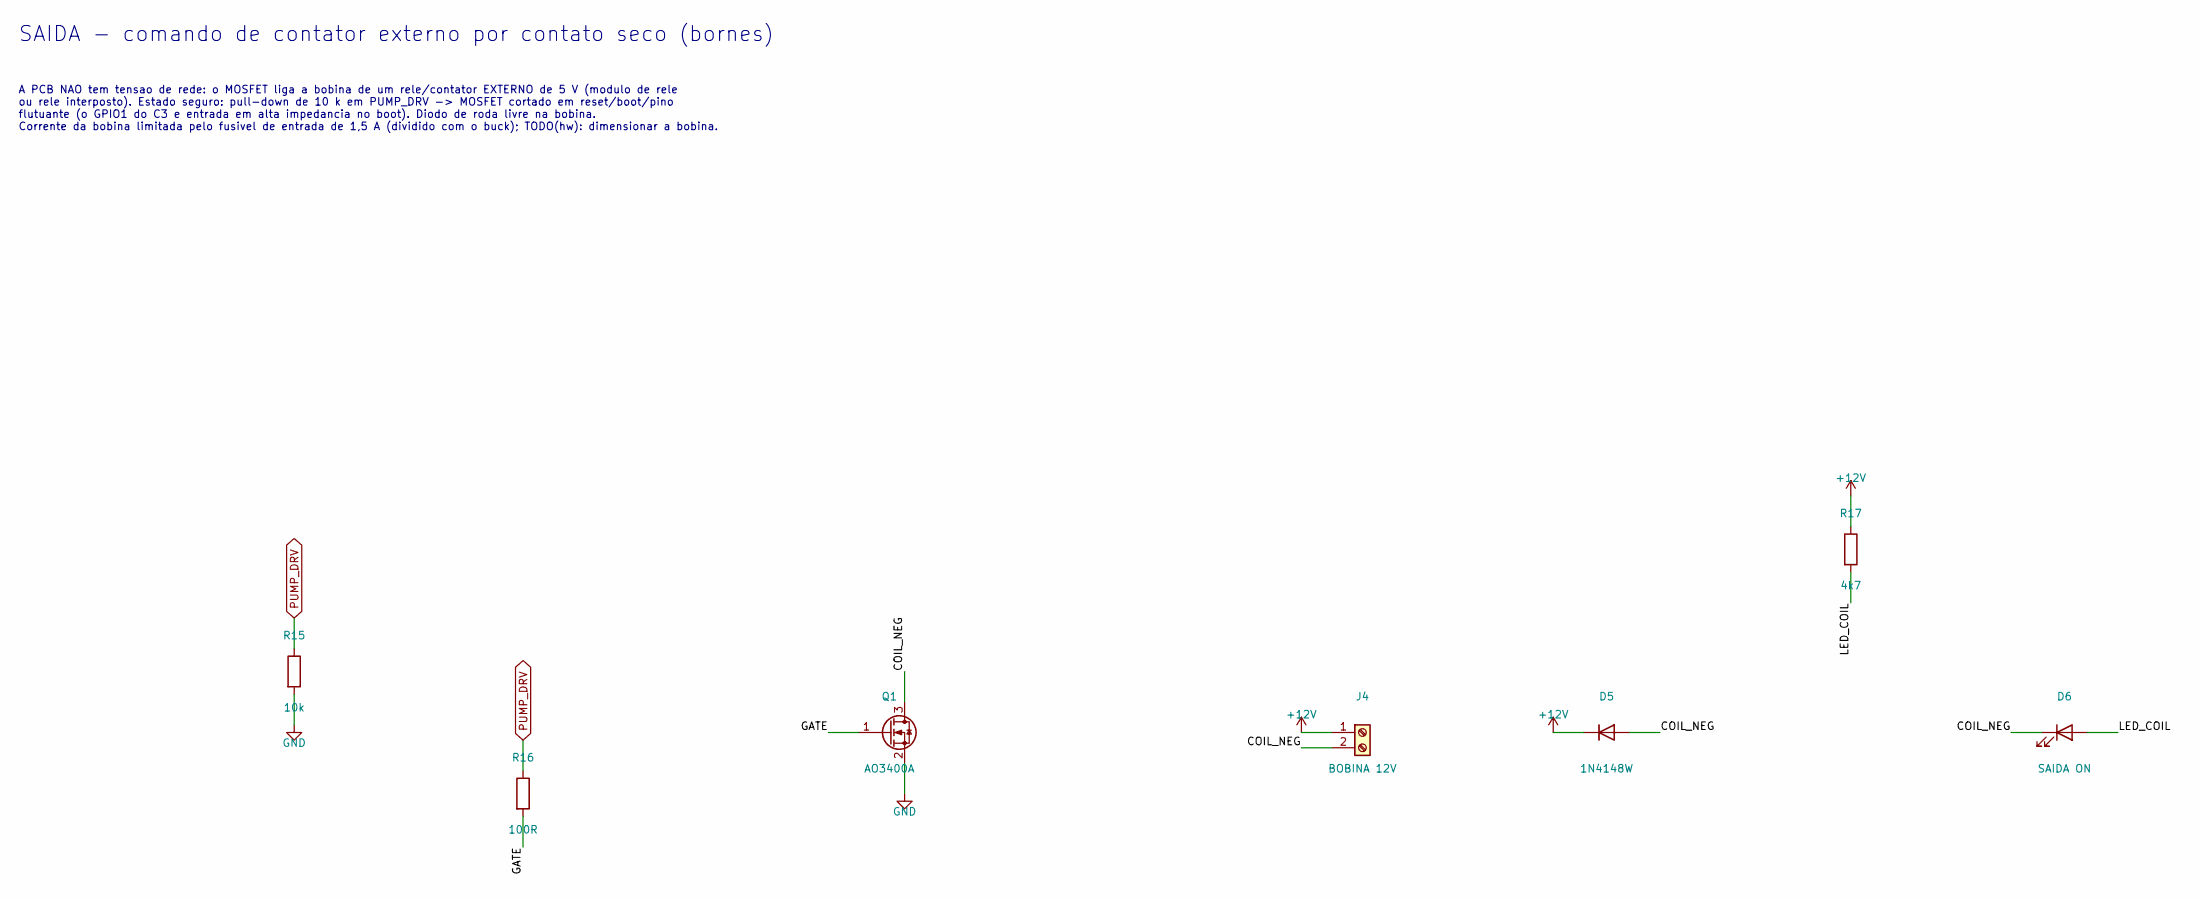
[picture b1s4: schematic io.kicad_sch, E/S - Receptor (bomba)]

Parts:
D5: 1N4148W; D_SOD-123; MPN 1N4148W
D6: SAIDA ON; LED_0603_1608Metric; MPN APT1608SGC
J4: BOBINA 12V; TerminalBlock_Phoenix_MKDS-1,5-2-5.08_1x02_P5.08mm_Horizont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; MPN MKDS 1,5/2-5,08
Q1: AO3400A; SOT-23; MPN AO3400A
R15: 10k; R_0603_1608Metric; MPN RC0603FR-0710KL
R16: 100R; R_0603_1608Metric; MPN RC0603FR-07100RL
R17: 4k7; R_0603_1608Metric; MPN RC0603FR-074K7L

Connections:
+12V: D5.1 (K), J4.1, R17.1; also elsewhere on the board
/Entradas e Saidas/COIL_NEG: D5.2 (A), D6.1 (K), J4.2, Q1.3 (D)
/Entradas e Saidas/GATE: Q1.1 (G), R16.2
/Entradas e Saidas/LED_COIL: D6.2 (A), R17.2
GND: Q1.2 (S), R15.2; also elsewhere on the board
PUMP_DRV: R15.1, R16.1; also elsewhere on the board

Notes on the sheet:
SAIDA - comando de contator externo por contato seco (bornes)
A PCB NAO tem tensao de rede: o MOSFET liga a bobina de um rele/contator EXTERNO de 5 V (modulo de rele ou rele interposto). Estado seguro: pull-down de 10 k em PUMP_DRV -> MOSFET cortado em reset/boot/pino flutuante (o GPIO1 do C3 e entrada em alta impedancia no boot). Diodo de roda livre na bobin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

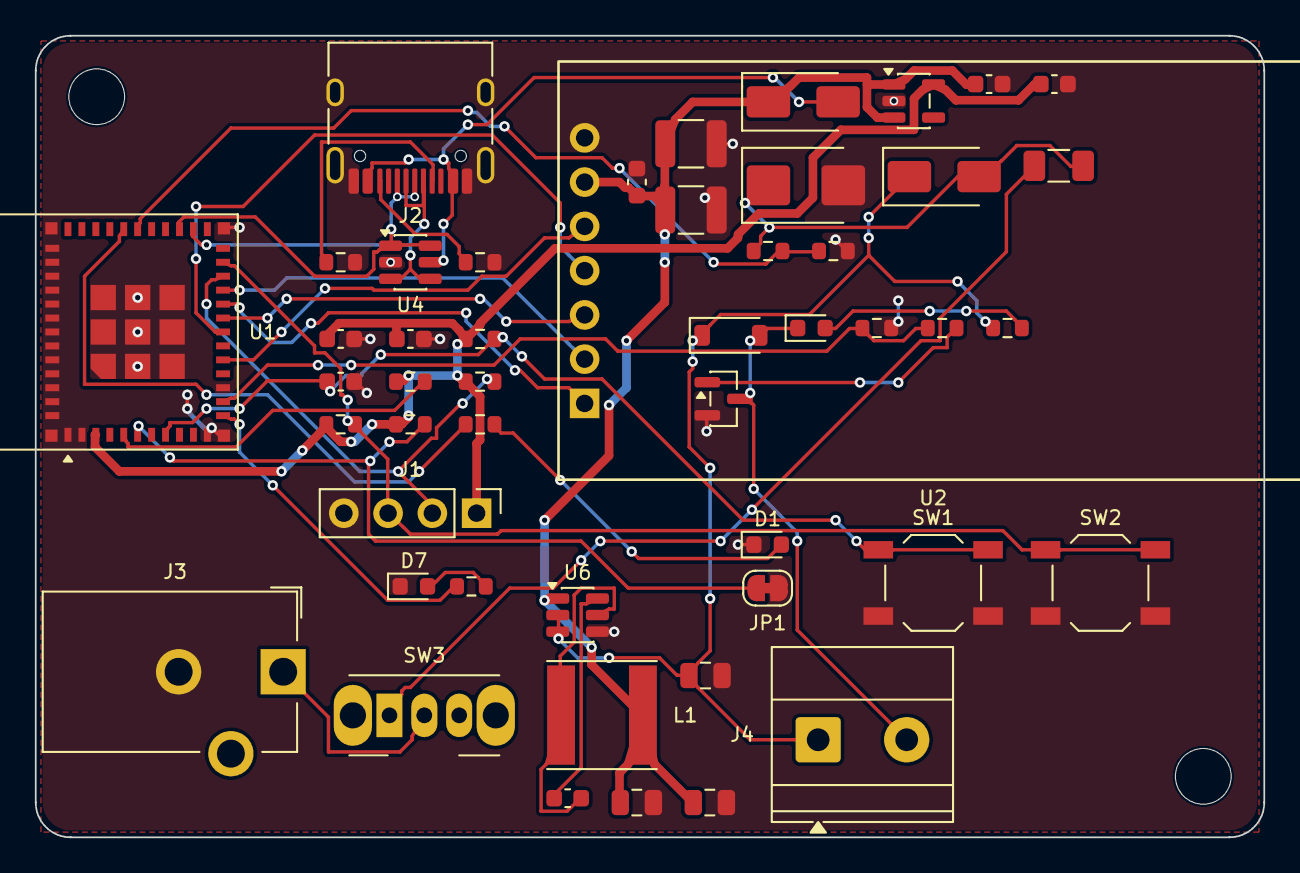
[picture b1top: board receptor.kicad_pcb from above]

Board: 2 copper layers, 70.5 x 46.0 mm, 51 parts (0 on the bottom side), 33 nets.

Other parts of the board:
H1, H2: MountingHole_3.2mm_M3

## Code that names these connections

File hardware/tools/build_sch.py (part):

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ROLES = {
    "emissor": {"titulo": "Emissor (reservatorio)", "gpio1": "FLOAT_LOW",
                "root": "7f0c2b1e-5a3d-4c8e-9b1a-2d4e6f802001", "n": 2},
    "receptor": {"titulo": "Receptor (bomba)", "gpio1": "PUMP_DRV",
                 "root": "7f0c2b1e-5a3d-4c8e-9b1a-2d4e6f803001", "n": 3},
}
COMMON_GLOBALS = {
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                    "GPIO18/19 = USB Serial/JTAG. GPIO20/21 = UART0 (console): ver decisoes.md.")
    sh.add("lora-pump:ESP32-C3-MINI-1", LIB, "U1", "ESP32-C3-MINI-1-H4X", 210, 150, {
        "3": "+3V3", "1": "GND",
        "8": "MCU_EN", "13": c.gpio1, "5": "FLOAT_HIGH",
        "6": "ROLE_STRAP", "18": "E220_TXD", "19": "E220_RXD", "20": "E220_M0",
        "21": "E220_M1", "22": "I2C_SDA", "23": "I2C_SCL", "16": "E220_AUX",
        "26": "USB_DM", "27": "USB_DP", "30": "EXT_PRESENT", "31": "LED_STATUS_DRV",
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            "Buck AP63205 (5,0 V fixo, 2 A, Vin 3,8-32 V; Datasheet Diodes DS41326, p.13, Tabela 3): L = 4,7 uH, C1 = 10 uF, C2 = 2 x 22 uF, C3 = 100 nF.\n"
            "LDO AP2112K-3.3: 600 mA min, Cin = Cout = 1 uF X5R/X7R (Datasheet Diodes, p.2). CC1/CC2 do USB-C com 5k1 (UFP).\n"
            "USB-C alimenta so a logica (Schottky D2, ~4,6 V): o E220 em 5,0 V exige o jack. TODO(hw): bateria 18650 + carregador na hw-v0.2.\n"
            "EXT_PRESENT: divisor 100k/33k do 12 V (~3 V no GPIO20). Sem bateria na hw-v0.1: GPIO0 livre.")
    # USB-C
    sh.add("Connector:USB_C_Receptacle_USB2.0_16P", "Connector.kicad_sym", "J2", "USB-C", 60, 120,
           {"A4": "VBUS", "A9": "VBUS", "B4": "VBUS", "B9": "VBUS",
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        sh.text(15, 12, "ENTRADAS - 2 boias (chave seca para GND)", 2.5)
        sh.text(15, 22,
                "Cada entrada: TVS no borne, 1 k em serie e 100 nF ao GND (filtro RC) e pull-up de 10 k para 3V3.\n"
                "Boia baixa -> GPIO1 (FLOAT_LOW). Boia alta -> GPIO2 (FLOAT_HIGH, pull-up R2 na folha MCU).\n"
                "Fechada = GND (tabela de histerese em assets/schematic.md). Sem sensor ultrassonico nesta revisao.")
        sh.add("Connector:Screw_Terminal_01x04", "Connector.kicad_sym", "J4", "BOIAS", 60, 130,
               {"1": "FLOAT_LOW_IN", "2": "GND", "3": "FLOAT_HIGH_IN", "4": "GND"},
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        sh.text(15, 12, "SAIDA - comando de contator externo por contato seco (bornes)", 2.5)
        sh.text(15, 22,
                "A PCB NAO tem tensao de rede: o MOSFET liga a bobina de um rele/contator EXTERNO de 5 V (modulo de rele\n"
                "ou rele interposto). Estado seguro: pull-down de 10 k em PUMP_DRV -> MOSFET cortado em reset/boot/pino\n"
                "flutuante (o GPIO1 do C3 e entrada em alta impedancia no boot). Diodo de roda livre na bobina.\n"
                "Corrente da bobina limitada pelo fusivel de entrada de 1,5 A (dividido com o buck); TODO(hw): dimensionar a bobina.")
        R(sh, c, "R15", "10k", 60, 120, "PUMP_DRV", "GND")
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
